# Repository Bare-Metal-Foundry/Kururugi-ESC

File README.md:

# ⚡ Kururugi - Electronic Speed Controller (ESC) ⚡ 

> 4/6S-ready • 64–96 kHz PWM • FOC/Six-Steps • Full bare-metal control

<p align="center">

  <br>

</p>

## ⚙️ Project overview

Kururugi is a high-performance ESC designed for FPV drones, built as a platform for low-level motor control, power electronics optimization, and embedded system experimentation.

It is developed within the **Bare Metal Foundry** initiative for autonomous racing drones, alongside the Shirley Flight Controller - forming a complete, fully controlled hardware and software stack.

This README provides an overview of the project and repository structure. Detailed hardware and ESC design information is available in: 📊 [Technical Specifications](docs/hw-kururugi-specs.md)

## ❓ Why Kururugi?

Most ESCs are closed, optimized for mass production - not understanding.

Kururugi is designed to:
- Push switching frequency limits (64 kHz in v1.0, targeting 96 kHz+ in future revisions)
- Provide full transparency and control over the motor stack (no black boxes)
- Enable high-speed bare-metal control
- Serve as a platform for developing and validating Six-Step and Field-Oriented Control (FOC)
- Bring together makers and engineers to explore, experiment, and push boundaries

👉 This is an research platform, not just an ESC.

## 🚢 Navigate the repo

> ⚠️ Documentation is still a work in progress. Detailed design notes and analysis will be added progressively.

### 📂 Not to miss documents:
- 🧩 **Hardware (KiCad)**: [KiCad project](hardware/Kururugi-ESC-KiCad/)
- 📊 **Design & Sizing**: [Design notes](docs\Kururugi-ESC-sizing.xlsx)
- 📊 **Technicals specifications**: [Documentation](docs/hw-kururugi-specs.md)
- 📤 **Exports**: [Schematics, PCB renders, STEP files](docs/exports)
- 📚 **Resources**: [Datasheets & Engineering Notes](resources/datasheets)

## 💻 Run it yourself

### 📟 H/W - PCB desgin
To get started, simply clone the repository and proceed to open the project on Kicad 9.0.4. All libraries are self containts so it is no more difficult than this.
```bash
git clone https://github.com/StepaneBinon/Kururugi-ESC-Dev-Board.git
```

### 📟 H/W — PCB Manufacturing

PCB fabrication and assembly are handled through JLCPCB. The minimum order quantity is 5 boards for PCB fabrication and 2 boards for assembly. With the selected options, the total cost is 255.13 € (295.01 USD).

Production files are available in [Production files](hardware/Kururugi-ESC-KiCad/Production/).  
When placing the order, use the parameters shown in [JLCPCB Options](hardware/Kururugi-ESC-KiCad/Production/JLCPCB%20-%20Options%20to%20use.png).

> ⚠️ Ensure BOM/CPL match and components are available before ordering.
> ⚠️ This design is provided as-is; no guarantee is made regarding functionality or performance.

### 🔢 S/W - Kururugi-6Step [WORK IN PROGRESS]

### 🔢 S/W - Kururugi-FOC [WORK IN PROGRESS]

## 🚀 Roadmap

### ⚡ Hardware
1. 🧪 **V1.0 Production & Bring-up** *(Apr 2026)*: First batch with JLCPCB, full electrical validation
2. 📖 **Design Documentation** *(May 2026)*: Complete breakdown of sizing, losses, and trade-offs
3. 🔌 **Multi-ESC Test Bench** *(Jun–Jul 2026)*: Dedicated rig for synchronized testing and stress scenarios
4. 🏁 **Drone Validation (V1)** *(Jul–Aug 2026)*: High-load FPV testing on 6-inch platform
5. 🤖 **Robotics Validation (V1)** *(Jul–Aug 2026)*: Differential drive platform for control robustness
6. 📝 **Technical Paper (V1 Results)** *(Sep 2026)*: Performance, efficiency, and design insights
7. ⚡ **V2 Hardware** *(2027)*: Sensor simplification, FOC/6-step optimization, possible 4-in-1

### 🧠 Software
1. 🏗 **Bare-Metal C++ Architecture** *(Apr–May 2026)*: Deterministic design, coding standards, HAL strategy (rewrite vs minimal use)
2. ⚙️ **6-Step Control (Baseline)** *(May–Jun 2026)*: Reliable startup and fallback mode
3. 🎯 **FOC Implementation** *(Jun–Aug 2026)*: High-efficiency, high-performance control
4. 📝 **Technical Paper (Control & Results)** *(Sep 2026)*: Control strategy, tuning, and comparison

## 🤝 How to Contribute

> Alone we go faster, together we go further.

Contributions are more than welcome, at all levels:

- 🐛 **Report issues**: bugs, design flaws, or unclear documentation
- 💡 **Suggest improvements**: hardware, firmware, or architecture ideas
- 🧪 **Test & validate**: share results, measurements, or flight data
- 📖 **Improve documentation**: clarify concepts, add explanations

### 📬 Get involved

- Open an issue for discussion  
- Submit a pull request  
- Share your insights or experiments 
- Join the **Bare Metal Foundry** discord here: https://discord.gg/e7CF2AZCN 

👉 If you're working on ESCs, power electronics, or embedded control, your feedback is highly valuable.

## 🪪 Licensing

### Hardware
Hardware design (schematics, PCB, KiCad) is licensed under CERN-OHL-S v2. This project is released as open hardware.
Any modifications or derived designs must be shared under the same license.

For commercial use, collaboration, or licensing inquiries, please reach out.

## 👤 Author

This project was originally created and is actively maintained by [Stepane Binon](https://github.com/StepaneBinon).

Parts of the documentation are generated with the assistance of AI tools to streamline development.

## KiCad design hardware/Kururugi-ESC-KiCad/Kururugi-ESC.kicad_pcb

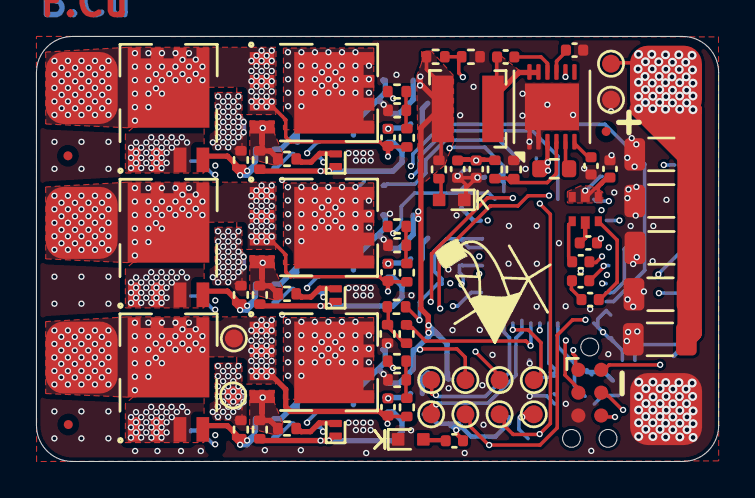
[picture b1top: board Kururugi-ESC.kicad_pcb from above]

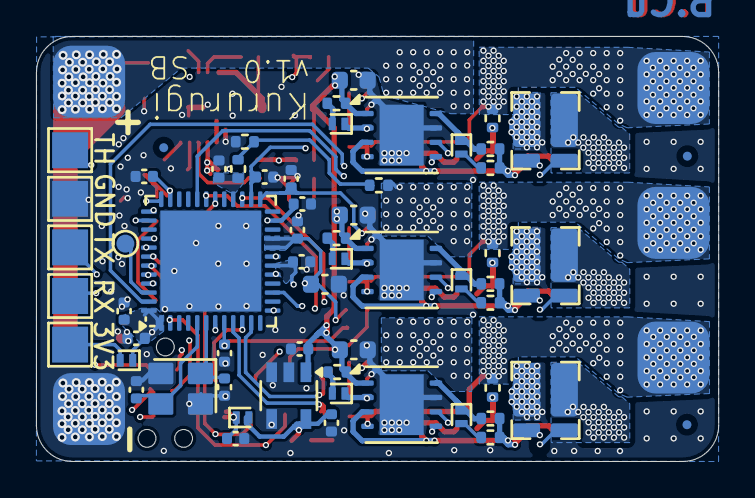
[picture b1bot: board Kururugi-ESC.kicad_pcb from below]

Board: 6 copper layers, 37.9 x 23.6 mm, 141 parts (60 on the bottom side), 85 nets.

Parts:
C1, C2, C3, C4, C5: 2.2u; C_1206_3216Metric
C6, C7, C8, C9, C15, C23, C24, C27, C30, C33: 100n; C_0402_1005Metric
C10, C11, C13, C14, C18, C21, C22: 1u; C_0402_1005Metric
C12, C16: 10n; C_0402_1005Metric
C17, C26, C29, C32: 1u; C_0603_1608Metric
C19, C20: 10p; C_0402_1005Metric
C25, C28, C31: 220n; C_0402_1005Metric
D1, D4: KT-0603W; LED_0603_1608Metric
D2, D3, D5, D6, D7, D8, D9, D10, D11, D12, D13: RB161QS-40T18R; Rohm_SMD1006
FID1, FID2, FID3, FID4, FID5, FID6: Fiducial_0.5mm_Mask1mm
J1, J2, J9, J10, J11: Conn_01x01; Phase4x4
J3, J4, J5, J6, J7: Conn_01x01; TestPoint_Pad_2.0x2.0mm
J8: JTAG_TC2030; Tag-Connect_TC2030-IDC-NL_2x03_P1.27mm_Vertical
L1: 22u; LVS404018-220M-N
LED1: 19-337C/RSBHGHC-A88/4T; SMD-B_19-337C_EVE
Q1, Q2, Q3, Q4, Q5, Q6: CSD18540Q5B
R1, R8: 22k; R_0402_1005Metric
R2, R12, R26, R37, R48: 33; R_0402_1005Metric
R3, R6, R27, R38, R49: 1k; R_0402_1005Metric
R4: 120k; R_0603_1608Metric
R5: 200k; R_0402_1005Metric
R7: 51k; R_0402_1005Metric
R9: 12k; R_0402_1005Metric
R10, R13, R14, R15, R16: 100; C_0402_1005Metric
R11, R20, R23, R24, R31, R34, R35, R42, R45, R46: 10k; R_0402_1005Metric
R17, R19, R21, R28, R30, R32, R39, R41, R43: 3.3; R_0402_1005Metric
R18, R22, R29, R33, R40, R44: 10; R_0402_1005Metric
R25, R36, R47: 0.5m; HoBB1216-5W-0.5mR-1
TH1: Thermistor_NTC; R_0402_1005Metric
TP1, TP2, TP3, TP4, TP5, TP6, TP7, TP8, TP9, TP10, TP11, TP12, TP13: TestPoint; TestPoint_Pad_D1.0mm
U1: STM32G474CEU6
U2: LM5160A; LM5160ADNTR
U3: TPS7B92033; TI-SOT-23 (5p)
U4, U5, U6: 2EDL8024
X1: 16MHz; YXC-X322516MLB4SI

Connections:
3V3: C7.1, C8.1, C9.1, C15.1, C16.1, C17.1, C18.2, C24.1, D2.1 (K), D3.1 (K), J8.1 (VCC), LED1.2, LED1.4, LED1.6, R11.1, TP13.1, U1.1 (VBAT), U1.20 (VREF+), U1.21 (VDDA), U1.23 (VDD), U1.35 (VDD), U1.48 (VDD)
3V3_UART: D2.2 (A), J5.1
/3V3_LDO: C21.1, D3.2 (A), R10.1, U3.5 (OUT)
/BOOT0: TP1.1, U1.46 (PB8-BOOT0)
/FB: R7.2, R9.1, U2.8 (FB)
/HSE_IN: C19.1, U1.5 (PF0-OSC_IN), X1.3
/HSE_OUT: C20.1, U1.6 (PF1-OSC_OUT), X1.1
/ISENS1+: R25.1, U1.17 (PB0)
/ISENS1-: R25.4, U1.19 (PB2)
/ISENS2+: R36.1, U1.15 (PA7)
/ISENS2-: R36.4, U1.13 (PA5)
/ISENS3+: R47.1, TP7.1, U1.9 (PA1)
/ISENS3-: R47.4, TP9.1, U1.11 (PA3)
/JTAG_NRST: J8.3 (~RESET), U1.7 (PG10-NRST)
/OPAMP_VOUT_ISENS3: TP8.1, U1.10 (PA2)
/PHASE 1/GH: Q1.2 (G), R18.2, R19.2, R20.1
/PHASE 1/GL: Q2.2 (G), R21.2, R22.2, R23.1
/PHASE 1/HB: C25.1, D5.1 (K), U4.2 (HB)
/PHASE 1/HO: D6.1 (K), R19.1, U4.3 (HO)
/PHASE 1/LO: D7.1 (K), R21.1, U4.8 (LO)
/PHASE 1/LS: Q2.3 (S), R25.2
/PHASE 1/VS: R24.2, R26.2, R27.2
/PHASE 2/GH: Q3.2 (G), R29.2, R30.2, R31.1
/PHASE 2/GL: Q4.2 (G), R32.2, R33.2, R34.1
/PHASE 2/HB: C28.1, D8.1 (K), U5.2 (HB)
/PHASE 2/HO: D9.1 (K), R30.1, U5.3 (HO)
/PHASE 2/LO: D10.1 (K), R32.1, U5.8 (LO)
/PHASE 2/LS: Q4.3 (S), R36.2
/PHASE 2/VS: R35.2, R37.2, R38.2
/PHASE 3/GH: Q5.2 (G), R40.2, R41.2, R42.1
/PHASE 3/GL: Q6.2 (G), R43.2, R44.2, R45.1
/PHASE 3/HB: C31.1, D11.1 (K), U6.2 (HB)
/PHASE 3/HO: D12.1 (K), R41.1, U6.3 (HO)
/PHASE 3/LO: D13.1 (K), R43.1, U6.8 (LO)
/PHASE 3/LS: Q6.3 (S), R47.2
/PHASE 3/VS: R46.2, R48.2, R49.2
/PWM1: U1.32 (PA10), U4.5 (HI)
/PWM1N: U1.47 (PB9), U4.6 (LI)
/PWM2: U1.31 (PA9), U5.5 (HI)
/PWM2N: U1.27 (PB14), U5.6 (LI)
/PWM3: TP6.1, U1.30 (PA8), U6.5 (HI)
/PWM3N: TP5.1, U1.2 (PC13), U6.6 (LI)
/RGB_B: R16.1, U1.42 (PB4)
/RGB_G: R15.1, U1.40 (PC11)
/RGB_R: R13.1, U1.43 (PB5)
/RON: R4.2, U2.5 (RON)
/SS: C14.1, U2.6 (SS)
/SW: C12.1, L1.1, U2.11 (SW), U2.12 (SW)
/SWCLK: J8.4 (SWCLK), U1.37 (PA14)
/SWDIO: J8.2 (SWDIO), U1.36 (PA13)
/SWO: J8.6 (SWO), U1.41 (PB3)
/THROTTLE_CMD: J6.1, U1.38 (PA15)
/TSENS: C23.1, R12.1, U1.8 (PA0)
/UART_RX: J3.1, U1.45 (PB7)
/UART_TX: J4.1, U1.44 (PB6)
/UVLO: R5.2, R8.1, U2.4 (EN/UVLO)
/VCC: C13.1, U2.9 (VCC)
/VSENS1: C27.1, R26.1, U1.26 (PB13)
/VSENS2: C30.1, R37.1, U1.25 (PB12)
/VSENS3: C33.1, R48.1, TP11.1, U1.18 (PB1)
/VSENSBAT: C6.1, R2.1, U1.28 (PB15)
GND: C1.2, C2.2, C3.2, C4.2, C5.2, C6.2, C7.2, C8.2, C9.2, C10.2, C11.2, C13.2, C14.2, C15.2, C16.2, C17.2, C18.1, C19.2, C20.2, C21.2, C22.2, C23.2, C24.2, C26.2, C27.2, C29.2, C30.2, C32.2, C33.2, D1.1 (K), D4.1 (K), J2.1, J7.1, J8.5 (GND), R3.2, R8.2, R9.2, R23.2, R25.3, R27.1, R34.2, R36.3, R38.1, R45.2, R47.3, R49.1, TH1.2, TP3.1, TP4.1, U1.PAD (VSS), U2.1 (AGND), U2.2 (PGND), U2.PAD (AGND), U3.2 (GND), U3.3 (NC), U3.4 (NC), U4.7 (VSS), U4.PAD (VSS), U5.7 (VSS), U5.PAD (VSS), U6.7 (VSS), U6.PAD (VSS), X1.2, X1.4
unnamed: D1.2 (A), R6.2
unnamed: D4.2 (A), R10.2
unnamed: D5.2 (A), R17.2
unnamed: D6.2 (A), R18.1
unnamed: D7.2 (A), R22.1
unnamed: D8.2 (A), R28.2
unnamed: D9.2 (A), R29.1
unnamed: D10.2 (A), R33.1
unnamed: D11.2 (A), R39.2
unnamed: D12.2 (A), R40.1
unnamed: D13.2 (A), R44.1
unnamed: LED1.1, R14.1
unnamed: LED1.3, R15.2
unnamed: LED1.5, R16.2
unnamed: R1.2, R2.2, R3.1
unnamed: R11.2, R12.2, TH1.1
unnamed: R13.2, R14.2
unnamed: C12.2, U2.10 (BST)
PH1: C25.2, J9.1, Q1.3 (S), Q2.1 (D), R20.2, R24.1, U4.4 (HS)
PH2: C28.2, J10.1, Q3.3 (S), Q4.1 (D), R31.2, R35.1, U5.4 (HS)
PH3: C31.2, J11.1, Q5.3 (S), Q6.1 (D), R42.2, R46.1, TP12.1, U6.4 (HS)
VBAT: C1.1, C2.1, C3.1, C4.1, C5.1, C10.1, C11.1, J1.1, Q1.1 (D), Q3.1 (D), Q5.1 (D), R1.1, R4.1, R5.1, TP2.1, U2.3 (VIN)
VBUCK: C22.1, C26.1, C29.1, C32.1, L1.2, R6.1, R7.1, R17.1, R28.1, R39.1, TP10.1, U3.1 (VIN), U4.1 (VDD), U5.1 (VDD), U6.1 (VDD)

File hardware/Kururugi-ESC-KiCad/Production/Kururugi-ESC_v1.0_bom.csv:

Designator,Footprint,Quantity,Value,LCSC Part #
"C1, C2, C3, C4, C5",1206,5,2.2u,C50254
"C10, C11, C13, C14, C18, C21, C22",0402,7,1u,C52923
"C12, C16",0402,2,10n,C15195
"C15, C23, C24, C27, C30, C33, C6, C7, C8, C9",0402,10,100n,C1525
"C17, C26, C29, C32",0603,4,1u,C15849
"C19, C20",0402,2,10p,C32949
"C25, C28, C31",0402,3,220n,C16772
"D1, D4",0603,2,KT-0603W,C2290
"D10, D11, D12, D13, D2, D3, D5, D6, D7, D8, D9",Rohm_SMD1006,11,RB161QS-40T18R, C2837790
"J1, J10, J11, J2, J9",Phase4x4,5,Conn_01x01,
"J3, J4, J5, J6, J7",TestPoint_Pad_2.0x2.0mm,5,Conn_01x01,
L1,LVS404018-220M-N,1,22u, C116614
LED1,SMD-B_19-337C_EVE,1,19-337C/RSBHGHC-A88/4T,C3019536
"Q1, Q2, Q3, Q4, Q5, Q6",CSD18540Q5B,6,CSD18540Q5B,C86513
"R1, R8",0402,2,22k,C25768
"R10, R13, R14, R15, R16",0402,5,100,C25076
"R11, R20, R23, R24, R31, R34, R35, R42, R45, R46",0402,10,10k,C25744
"R12, R2, R26, R37, R48",0402,5,33,C25105
"R17, R19, R21, R28, R30, R32, R39, R41, R43",0402,9,3.3,C25165
"R18, R22, R29, R33, R40, R44",0402,6,10,C25077
"R25, R36, R47",HoBB1216-5W-0.5mR-1,3,0.5m,C17701556
"R27, R3, R38, R49, R6",0402,5,1k,C11702
R4,0603,1,120k,C25808
R5,0402,1,200k,C25764
R7,0402,1,51k,C25794
R9,0402,1,12k,C25752
TH1,0402,1,Thermistor_NTC,C209959
"TP1, TP10, TP11, TP12, TP13, TP2, TP3, TP4, TP5, TP6, TP7, TP8, TP9",TestPoint_Pad_D1.0mm,13,TestPoint,
U1,STM32G474CEU6,1,STM32G474CEU6, C1235412
U2,LM5160ADNTR,1,LM5160A,C473375
U3,TI-SOT-23 (5p),1,TPS7B92033,C32353919
"U4, U5, U6",2EDL8024,3,2EDL8024, C3655215
X1,YXC-X322516MLB4SI,1,16MHz,C13738

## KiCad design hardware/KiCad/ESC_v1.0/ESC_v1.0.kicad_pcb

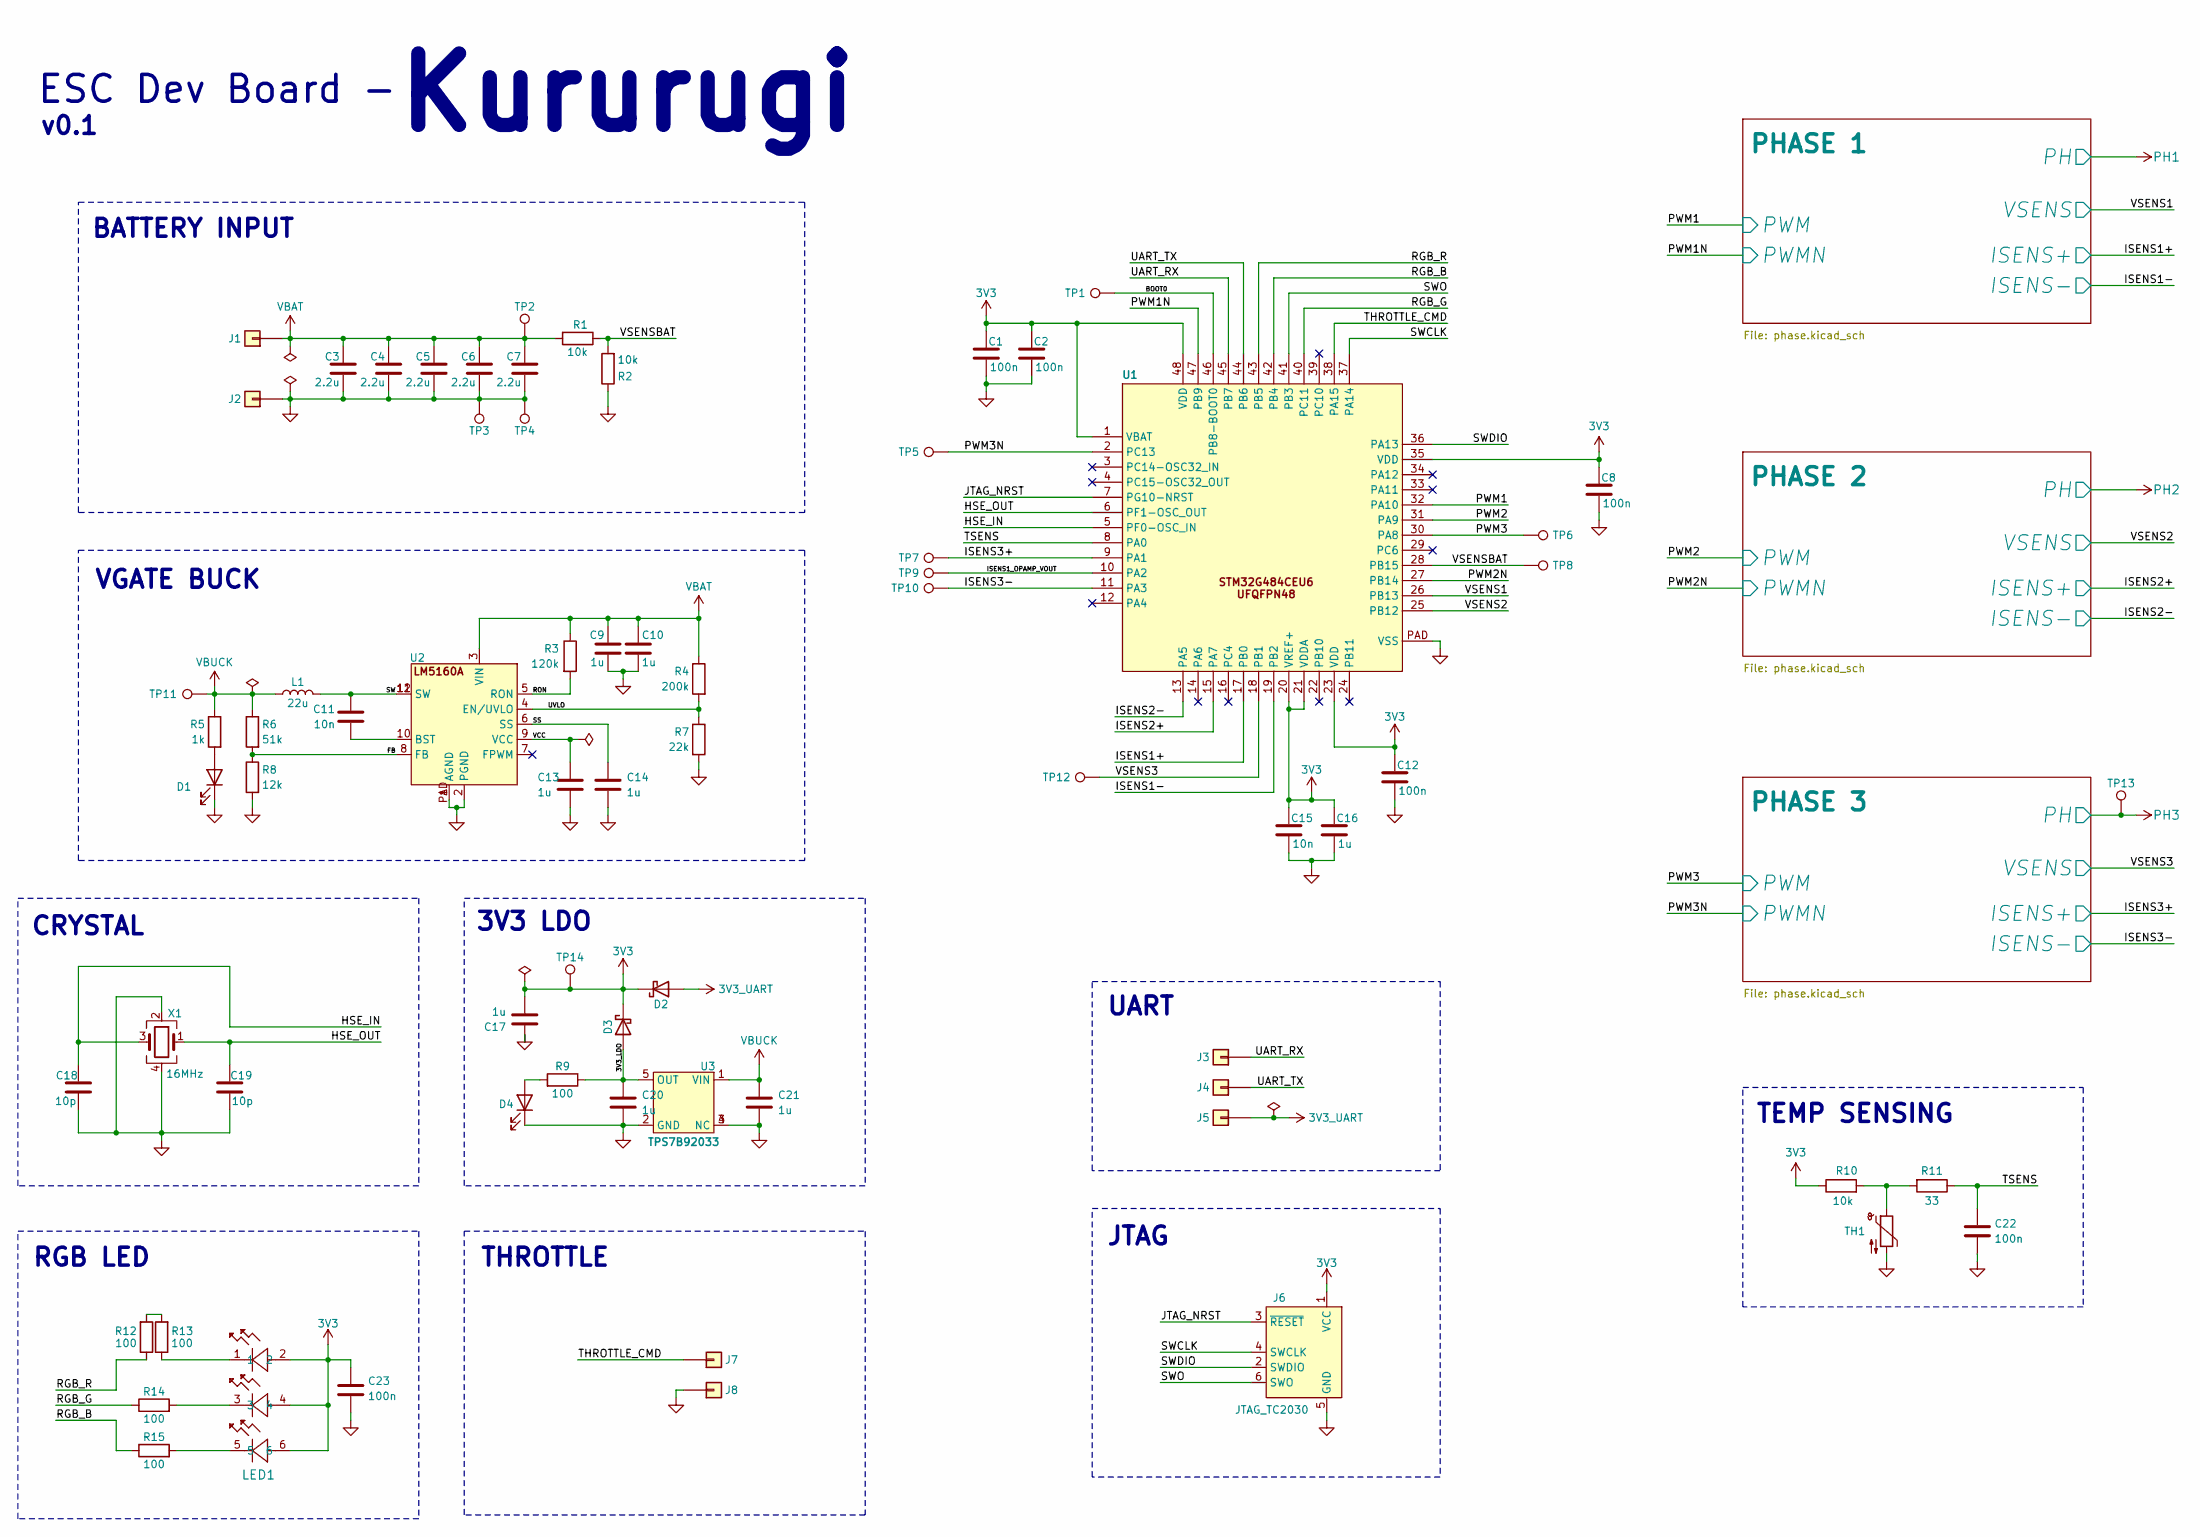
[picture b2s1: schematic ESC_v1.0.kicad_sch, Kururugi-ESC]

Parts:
C1, C2, C8, C12, C22, C23: 100n; C_0402_1005Metric; Manufacturer Part Number CL05B104KO5NNNC; LCSC C1525
C3, C4, C5, C6, C7: 2.2u; C_1206_3216Metric; Manufacturer Part Number CL31B225KBHNNNE; LCSC C50254
C9, C10, C13, C14, C17, C20, C21: 1u; C_0402_1005Metric; Manufacturer Part Number CL05A105KA5NQNC; LCSC C52923
C11, C15: 10n; C_0402_1005Metric; Manufacturer Part Number CL05B103KB5NNNC; LCSC C15195
C16: 1u; C_0603_1608Metric; Manufacturer Part Number CL10A105KB8NNNC; LCSC C15849
C18, C19: 10p; C_0402_1005Metric; Manufacturer Part Number CL05C100JB5NNNC; LCSC C32949
D1, D4: KT-0603W; LED_0603_1608Metric; Manufacturer Part Number KT-0603W; LCSC C2290
D2, D3: RB161QS-40T18R; Rohm_SMD1006; Manufacturer Part Number RB161QS-40T18R; LCSC C2837790
J1, J2: Conn_01x01; Phase4x4
J3, J4, J5, J7, J8: Conn_01x01; TestPoint_Pad_2.0x2.0mm
J6: JTAG_TC2030; Tag-Connect_TC2030-IDC-NL_2x03_P1.27mm_Vertical
L1: 22u; Chilisin_Elec_SMD,4x4mm; Manufacturer Part Number LVS404018-220M-N; LCSC C116614
LED1: 19-337C/RSBHGHC-A88/4T; SMD-B_19-337C_EVE; Manufacturer Part Number 19-337C/RSBHGHC-A88/4T; LCSC C3019536
R1, R2, R10: 10k; R_0402_1005Metric; Manufacturer Part Number 0402WGF1002TCE; LCSC C25744
R3: 120k; R_0603_1608Metric; Manufacturer Part Number 0603WAF1203T5E; LCSC C25808
R4: 200k; R_0402_1005Metric; Manufacturer Part Number 0402WGF2003TCE; LCSC C25764
R5: 1k; R_0402_1005Metric; Manufacturer Part Number 0402WGF1001TCE; LCSC C11702
R6: 51k; R_0402_1005Metric; Manufacturer Part Number 0402WGF5102TCE; LCSC C25794
R7: 22k; R_0402_1005Metric; Manufacturer Part Number 0402WGF2202TCE; LCSC C25768
R8: 12k; R_0402_1005Metric; Manufacturer Part Number 0402WGF1202TCE; LCSC C25752
R9, R12, R13, R14, R15: 100; R_0402_1005Metric; Manufacturer Part Number 0402WGF1000TCE; LCSC C25076
R11: 33; R_0402_1005Metric; Manufacturer Part Number 0402WGF330JTCE; LCSC C25752
TH1: Thermistor_NTC; R_0402_1005Metric; Manufacturer Part Number NTCG103JF103FT1; LCSC C209959
TP1, TP2, TP3, TP4, TP5, TP6, TP7, TP8, TP9, TP10, TP11, TP12, TP13, TP14: TestPoint; TestPoint_Pad_D1.0mm
U1: STM32G484CEU6; QFN-48-1EP_7x7mm_P0.5mm_EP5.6x5.6mm; Manufacturer Part Number STM32G484CEU6; LCSC C1342230
U2: LM5160A; WSON-12-1EP_4x4mm_P0.5mm_EP2.6x3mm; Manufacturer Part Number LM5160ADNTR; LCSC C473375
U3: TPS7B92033; TI-SOT-23 (5p); Manufacturer Part Number TPS7B92033DBVR; LCSC C32353919
X1: 16MHz; YXC-X322516MLB4SI; Manufacturer Part Number X322516MLB4SI; LCSC C13738

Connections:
3V3: C1.1, C2.1, C8.1, C12.1, C15.1, C16.1, C17.2, C23.1, D2.1 (K), D3.1 (K), J6.1 (VCC), LED1.2, LED1.4, LED1.6, R10.1, TP14.1, U1.1 (VBAT), U1.20 (VREF+), U1.21 (VDDA), U1.23 (VDD), U1.35 (VDD), U1.48 (VDD)
3V3_UART: D2.2 (A), J5.1
/3V3_LDO: C20.1, D3.2 (A), R9.1, U3.5 (OUT)
/BOOT0: TP1.1, U1.46 (PB8-BOOT0)
/FB: R6.2, R8.1, U2.8 (FB)
/HSE_IN: C18.1, U1.5 (PF0-OSC_IN), X1.3
/HSE_OUT: C19.1, U1.6 (PF1-OSC_OUT), X1.1
/ISENS1+: U1.17 (PB0); also elsewhere on the board
/ISENS1-: U1.19 (PB2); also elsewhere on the board
/ISENS1_OPAMP_VOUT: TP9.1, U1.10 (PA2)
/ISENS2+: U1.15 (PA7); also elsewhere on the board
/ISENS2-: U1.13 (PA5); also elsewhere on the board
/ISENS3+: TP7.1, U1.9 (PA1); also elsewhere on the board
/ISENS3-: TP10.1, U1.11 (PA3); also elsewhere on the board
/JTAG_NRST: J6.3 (~RESET), U1.7 (PG10-NRST)
/PWM1: U1.32 (PA10); also elsewhere on the board
/PWM1N: U1.47 (PB9); also elsewhere on the board
/PWM2: U1.31 (PA9); also elsewhere on the board
/PWM2N: U1.27 (PB14); also elsewhere on the board
/PWM3: TP6.1, U1.30 (PA8); also elsewhere on the board
/PWM3N: TP5.1, U1.2 (PC13); also elsewhere on the board
/RGB_B: R15.1, U1.42 (PB4)
/RGB_G: R14.1, U1.40 (PC11)
/RGB_R: R12.1, U1.43 (PB5)
/RON: R3.2, U2.5 (RON)
/SS: C14.1, U2.6 (SS)
/SW: C11.1, L1.1, U2.11 (SW), U2.12 (SW)
/SWCLK: J6.4 (SWCLK), U1.37 (PA14)
/SWDIO: J6.2 (SWDIO), U1.36 (PA13)
/SWO: J6.6 (SWO), U1.41 (PB3)
/THROTTLE_CMD: J7.1, U1.38 (PA15)
/TSENS: C22.1, R11.1, U1.8 (PA0)
/UART_RX: J3.1, U1.45 (PB7)
/UART_TX: J4.1, U1.44 (PB6)
/UVLO: R4.2, R7.1, U2.4 (EN/UVLO)
/VCC: C13.1, U2.9 (VCC)
/VSENS1: U1.26 (PB13); also elsewhere on the board
/VSENS2: U1.25 (PB12); also elsewhere on the board
/VSENS3: TP12.1, U1.18 (PB1); also elsewhere on the board
/VSENSBAT: R1.1, R2.2, TP8.1, U1.28 (PB15)
GND: C1.2, C2.2, C3.2, C4.2, C5.2, C6.2, C7.2, C8.2, C9.2, C10.2, C12.2, C13.2, C14.2, C15.2, C16.2, C17.1, C18.2, C19.2, C20.2, C21.2, C22.2, C23.2, D1.1 (K), D4.1 (K), J2.1, J6.5 (GND), J8.1, R2.1, R7.2, R8.2, TH1.2, TP3.1, TP4.1, U1.PAD (VSS), U2.1 (AGND), U2.2 (PGND), U2.PAD (AGND), U3.2 (GND), U3.3 (NC), U3.4 (NC), X1.2, X1.4; also elsewhere on the board
unnamed: D1.2 (A), R5.2
unnamed: D4.2 (A), R9.2
unnamed: LED1.1, R13.1
unnamed: LED1.3, R14.2
unnamed: LED1.5, R15.2
unnamed: R10.2, R11.2, TH1.1
unnamed: R12.2, R13.2
unnamed: C11.2, U2.10 (BST)
PH3: TP13.1; also elsewhere on the board
VBAT: C3.1, C4.1, C5.1, C6.1, C7.1, C9.1, C10.1, J1.1, R1.2, R3.1, R4.1, TP2.1, U2.3 (VIN); also elsewhere on the board
VBUCK: C21.1, L1.2, R5.1, R6.1, TP11.1, U3.1 (VIN); also elsewhere on the board

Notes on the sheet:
Kururugi
UART
JTAG
THROTTLE
RGB LED
CRYSTAL
BATTERY INPUT
VGATE BUCK
TEMP SENSING
ESC Dev Board -
3V3 LDO
${REVISION}

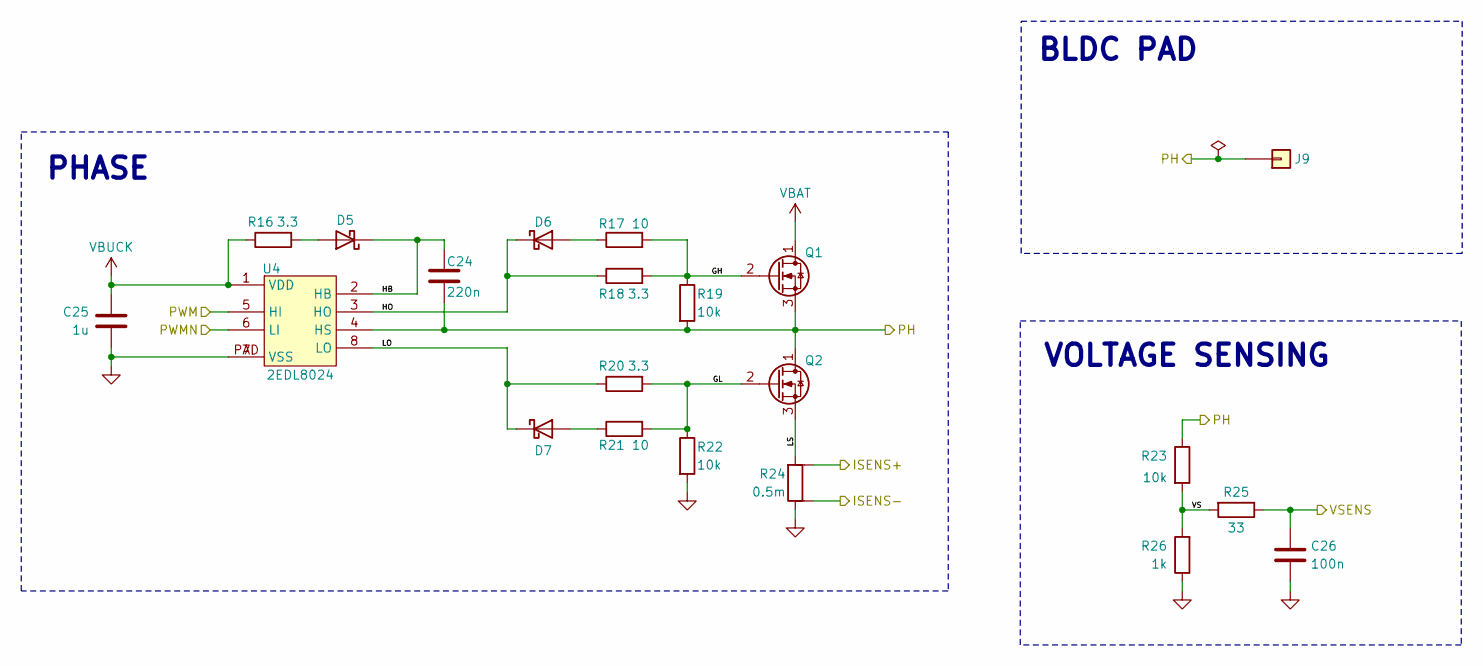
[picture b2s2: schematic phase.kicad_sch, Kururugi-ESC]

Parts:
C24: 220n; C_0402_1005Metric; Manufacturer Part Number CL05B224KO5NNNC; LCSC C16772
C25: 1u; C_0603_1608Metric; Manufacturer Part Number CL10A105KB8NNNC; LCSC C15849
C26: 100n; C_0402_1005Metric; Manufacturer Part Number CL05B104KO5NNNC; LCSC C1525
D5, D6, D7: RB161QS-40T18R; Rohm_SMD1006; Manufacturer Part Number RB161QS-40T18R; LCSC C2837790
J9: Conn_01x01; Phase4x4
Q1, Q2: CSD18540Q5B; TRANS_CSD18540Q5B; Manufacturer Part Number CSD18540Q5B; LCSC C86513
R16, R18, R20: 3.3; R_0402_1005Metric; Manufacturer Part Number 0402WGJ033JTCE; LCSC C25165
R17, R21: 10; R_0402_1005Metric; Manufacturer Part Number 0402WGF100JTCE; LCSC C25077
R19, R22, R23: 10k; R_0402_1005Metric; Manufacturer Part Number 0402WGF1002TCE; LCSC C25744
R24: 0.5m; Kelvin Shunt 1216 (3038); Manufacturer Part Number HoBB1216-5W-0.5mR-1%; LCSC C17701556
R25: 33; R_0402_1005Metric; Manufacturer Part Number 0402WGF330JTCE; LCSC C25752
R26: 1k; R_0402_1005Metric; Manufacturer Part Number 0402WGF1001TCE; LCSC C11702
U4: 2EDL8024; 2EDL8x2x_PG-VDSON-8-4; Manufacturer Part Number 2EDL8024G; LCSC C3655215

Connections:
/ISENS1+: R24.1; also elsewhere on the board
/ISENS1-: R24.4; also elsewhere on the board
/PHASE 1/GH: Q1.2 (G), R17.2, R18.2, R19.1
/PHASE 1/GL: Q2.2 (G), R20.2, R21.2, R22.1
/PHASE 1/HB: C24.1, D5.1 (K), U4.2 (HB)
/PHASE 1/HO: D6.1 (K), R18.1, U4.3 (HO)
/PHASE 1/LO: D7.1 (K), R20.1, U4.8 (LO)
/PHASE 1/LS: Q2.3 (S), R24.2
/PHASE 1/VS: R23.2, R25.2, R26.2
/PWM1: U4.5 (HI); also elsewhere on the board
/PWM1N: U4.6 (LI); also elsewhere on the board
/VSENS1: C26.1, R25.1; also elsewhere on the board
GND: C25.2, C26.2, R22.2, R24.3, R26.1, U4.7 (VSS), U4.PAD (VSS); also elsewhere on the board
unnamed: D5.2 (A), R16.2
unnamed: D6.2 (A), R17.1
unnamed: D7.2 (A), R21.1
PH1: C24.2, J9.1, Q1.3 (S), Q2.1 (D), R19.2, R23.1, U4.4 (HS)
VBAT: Q1.1 (D); also elsewhere on the board
VBUCK: C25.1, R16.1, U4.1 (VDD); also elsewhere on the board

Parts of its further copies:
C27, C30: 220n; C_0402_1005Metric; Manufacturer Part Number CL05B224KO5NNNC; LCSC C16772
C28, C31: 1u; C_0603_1608Metric; Manufacturer Part Number CL10A105KB8NNNC; LCSC C15849
C29, C32: 100n; C_0402_1005Metric; Manufacturer Part Number CL05B104KO5NNNC; LCSC C1525
D8, D9, D10, D11, D12, D13: RB161QS-40T18R; Rohm_SMD1006; Manufacturer Part Number RB161QS-40T18R; LCSC C2837790
J10, J11: Conn_01x01; Phase4x4
Q3, Q4, Q5, Q6: CSD18540Q5B; TRANS_CSD18540Q5B; Manufacturer Part Number CSD18540Q5B; LCSC C86513
R27, R29, R31, R38, R40, R42: 3.3; R_0402_1005Metric; Manufacturer Part Number 0402WGJ033JTCE; LCSC C25165
R28, R32, R39, R43: 10; R_0402_1005Metric; Manufacturer Part Number 0402WGF100JTCE; LCSC C25077
R30, R33, R34, R41, R44, R45: 10k; R_0402_1005Metric; Manufacturer Part Number 0402WGF1002TCE; LCSC C25744
R35, R46: 0.5m; Kelvin Shunt 1216 (3038); Manufacturer Part Number HoBB1216-5W-0.5mR-1%; LCSC C17701556
R36, R47: 33; R_0402_1005Metric; Manufacturer Part Number 0402WGF330JTCE; LCSC C25752
R37, R48: 1k; R_0402_1005Metric; Manufacturer Part Number 0402WGF1001TCE; LCSC C11702
U5, U6: 2EDL8024; 2EDL8x2x_PG-VDSON-8-4; Manufacturer Part Number 2EDL8024G; LCSC C3655215

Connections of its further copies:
/ISENS2+: R35.1; also elsewhere on the board
/ISENS2-: R35.4; also elsewhere on the board
/ISENS3+: R46.1; also elsewhere on the board
/ISENS3-: R46.4; also elsewhere on the board
/PHASE 2/GH: Q3.2 (G), R28.2, R29.2, R30.1
/PHASE 2/GL: Q4.2 (G), R31.2, R32.2, R33.1
/PHASE 2/HB: C27.1, D8.1 (K), U5.2 (HB)
/PHASE 2/HO: D9.1 (K), R29.1, U5.3 (HO)
/PHASE 2/LO: D10.1 (K), R31.1, U5.8 (LO)
/PHASE 2/LS: Q4.3 (S), R35.2
/PHASE 2/VS: R34.2, R36.2, R37.2
/PHASE 3/GH: Q5.2 (G), R39.2, R40.2, R41.1
/PHASE 3/GL: Q6.2 (G), R42.2, R43.2, R44.1
/PHASE 3/HB: C30.1, D11.1 (K), U6.2 (HB)
/PHASE 3/HO: D12.1 (K), R40.1, U6.3 (HO)
/PHASE 3/LO: D13.1 (K), R42.1, U6.8 (LO)
/PHASE 3/LS: Q6.3 (S), R46.2
/PHASE 3/VS: R45.2, R47.2, R48.2
/PWM2: U5.5 (HI); also elsewhere on the board
/PWM2N: U5.6 (LI); also elsewhere on the board
/PWM3: U6.5 (HI); also elsewhere on the board
/PWM3N: U6.6 (LI); also elsewhere on the board
/VSENS2: C29.1, R36.1; also elsewhere on the board
/VSENS3: C32.1, R47.1; also elsewhere on the board
GND: C28.2, C29.2, C31.2, C32.2, R33.2, R35.3, R37.1, R44.2, R46.3, R48.1, U5.7 (VSS), U5.PAD (VSS), U6.7 (VSS), U6.PAD (VSS); also elsewhere on the board
unnamed: D8.2 (A), R27.2
unnamed: D9.2 (A), R28.1
unnamed: D10.2 (A), R32.1
unnamed: D11.2 (A), R38.2
unnamed: D12.2 (A), R39.1
unnamed: D13.2 (A), R43.1
PH2: C27.2, J10.1, Q3.3 (S), Q4.1 (D), R30.2, R34.1, U5.4 (HS)
PH3: C30.2, J11.1, Q5.3 (S), Q6.1 (D), R41.2, R45.1, U6.4 (HS); also elsewhere on the board
VBAT: Q3.1 (D), Q5.1 (D); also elsewhere on the board
VBUCK: C28.1, C31.1, R27.1, R38.1, U5.1 (VDD), U6.1 (VDD); also elsewhere on the board

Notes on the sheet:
PHASE
BLDC PAD
VOLTAGE SENSING

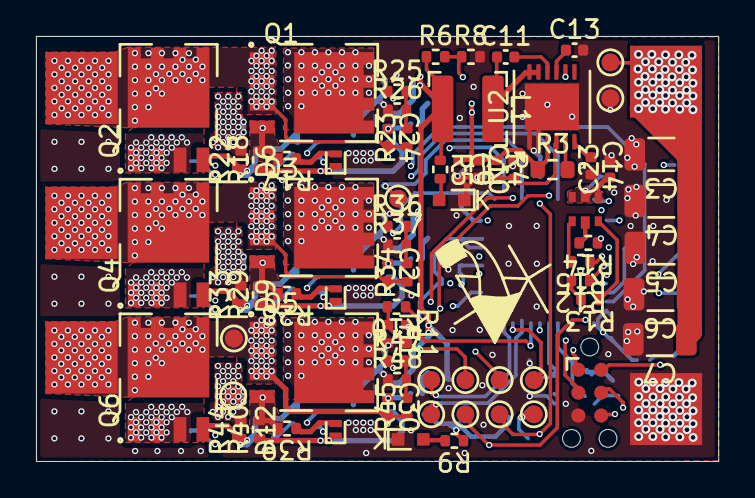
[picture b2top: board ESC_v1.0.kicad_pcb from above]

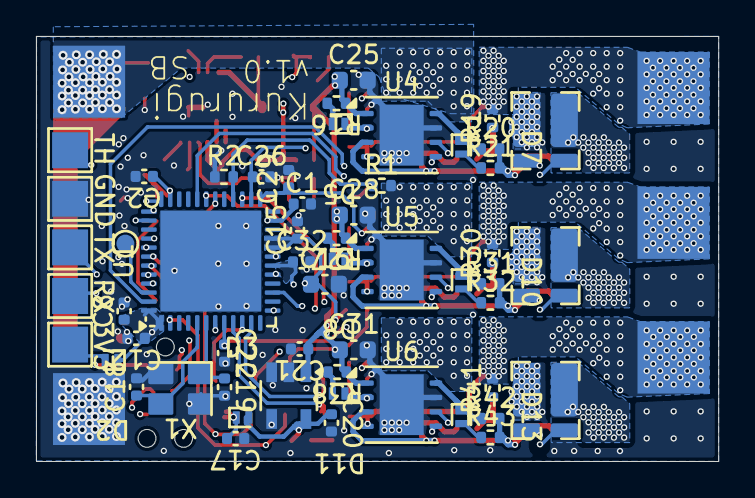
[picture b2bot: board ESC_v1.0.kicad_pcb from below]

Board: 6 copper layers, 37.9 x 23.6 mm, 134 parts (55 on the bottom side), 84 nets.

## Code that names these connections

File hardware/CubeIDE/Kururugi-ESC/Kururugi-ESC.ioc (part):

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Mcu.Name=STM32G484CEUx
Mcu.Package=UFQFPN48
Mcu.UserName=STM32G484CEUx
PA0.GPIOParameters=GPIO_Label
PA0.GPIO_Label=TSENS
PA0.Mode=IN1-Single-Ended
PA0.Signal=ADC2_IN1
PA1.GPIOParameters=GPIO_Label
PA1.GPIO_Label=AMP1VINP_ISENS3+
PA1.Mode=PGA Connected-INVERTINGINPUT_IO0_BIAS
PA1.Signal=OPAMP1_VINP
PA10.GPIOParameters=GPIO_Label
PA10.GPIO_Label=TIM1CH3_PH1
PA10.Signal=S_TIM1_CH3
PA13.GPIOParameters=GPIO_Label
PA13.GPIO_Label=SWDIO
PA13.Mode=Trace_Asynchronous_SW
PA13.Signal=SYS_JTMS-SWDIO
PA14.GPIOParameters=GPIO_Label
PA14.GPIO_Label=SWCLK
PA14.Mode=Trace_Asynchronous_SW
PA14.Signal=SYS_JTCK-SWCLK
PA15.GPIOParameters=GPIO_Label
PA15.GPIO_Label=TIM2CH1_TH
PA15.Signal=S_TIM2_CH1
PA2.GPIOParameters=GPIO_Label
PA2.GPIO_Label=AMP1VOUT_ISENS3
PA2.Mode=PGA Connected-INVERTINGINPUT_IO0_BIAS
PA2.Signal=OPAMP1_VOUT
PA3.GPIOParameters=GPIO_Label
PA3.GPIO_Label=AMP1VINM_ISENS3-
PA3.Mode=PGA Connected-INVERTINGINPUT_IO0_BIAS
PA3.Signal=OPAMP1_VINM0
PA5.GPIOParameters=GPIO_Label
PA5.GPIO_Label=AMP2VINM_ISENS2-
PA5.Mode=PGA Internally connected_IO
PA5.Signal=OPAMP2_VINM0
PA7.GPIOParameters=GPIO_Label
PA7.GPIO_Label=AMP2VINP_ISENS2+
PA7.Mode=PGA Internally connected_IO
PA7.Signal=OPAMP2_VINP
PA8.GPIOParameters=GPIO_Label
PA8.GPIO_Label=TIM1CH1_PH3
PA8.Signal=S_TIM1_CH1
PA9.GPIOParameters=GPIO_Label
PA9.GPIO_Label=TIM1CH2_PH2
PA9.Signal=S_TIM1_CH2
PB0.GPIOParameters=GPIO_Label
PB0.GPIO_Label=AMP3VINP_ISENS1+
PB0.Mode=PGA Internally connected_IO
PB0.Signal=OPAMP3_VINP
PB1.GPIOParameters=GPIO_Label
PB1.GPIO_Label=ADC1IN12_VSENS3
PB1.Mode=IN12-Single-Ended
PB1.Signal=ADC1_IN12
PB12.GPIOParameters=GPIO_Label
PB12.GPIO_Label=ADC4IN3_VSENS2
PB12.Mode=IN3-Single-Ended
PB12.Signal=ADC4_IN3
PB13.GPIOParameters=GPIO_Label
PB13.GPIO_Label=ADC3IN5_VSENS1
PB13.Mode=IN5-Single-Ended
PB13.Signal=ADC3_IN5
PB14.GPIOParameters=GPIO_Label
PB14.GPIO_Label=TIM1CH2N_PH2N
PB14.Mode=PWM Generation2 CH2 CH2N
PB14.Signal=TIM1_CH2N
PB15.GPIOParameters=GPIO_Label
PB15.GPIO_Label=ADC4IN5_VBATSENS
PB15.Mode=IN5-Single-Ended
PB15.Signal=ADC4_IN5
PB2.GPIOParameters=GPIO_Label
PB2.GPIO_Label=AMP3VINM_ISENS1-
PB2.Mode=PGA Internally connected_IO
PB2.Signal=OPAMP3_VINM0
PB3.GPIOParameters=GPIO_Label
PB3.GPIO_Label=SWO
PB3.Mode=Trace_Asynchronous_SW
PB3.Signal=SYS_JTDO-SWO
PB4.GPIOParameters=GPIO_Label
PB4.GPIO_Label=RGB_B
PB4.Signal=GPIO_Output
PB5.GPIOParameters=GPIO_Label
PB5.GPIO_Label=RGB_R
PB5.Signal=GPIO_Output
PB6.GPIOParameters=GPIO_Label
PB6.GPIO_Label=UART_TX
PB6.Mode=Asynchronous
PB6.Signal=USART1_TX
PB7.GPIOParameters=GPIO_Label
PB7.GPIO_Label=UART_RX
PB7.Mode=Asynchronous
PB7.Signal=USART1_RX
PB9.GPIOParameters=GPIO_Label
PB9.GPIO_Label=TIM1CH3N_PH1N
PB9.Mode=Output Compare3 CH3 CH3N
PB9.Signal=TIM1_CH3N
PC11.GPIOParameters=GPIO_Label
PC11.GPIO_Label=RGB_G
PC11.Signal=GPIO_Output
PC13.GPIOParameters=GPIO_Label
PC13.GPIO_Label=TIM1CH1N_PH3N
PC13.Mode=Output Compare1 CH1 CH1N
PC13.Signal=TIM1_CH1N
PF0-OSC_IN.GPIOParameters=GPIO_Label
PF0-OSC_IN.GPIO_Label=HSE_IN
PF0-OSC_IN.Mode=HSE-External-Oscillator
PF0-OSC_IN.Signal=RCC_OSC_IN
PF1-OSC_OUT.GPIOParameters=GPIO_Label
PF1-OSC_OUT.GPIO_Label=HSE_OUT
PF1-OSC_OUT.Mode=HSE-External-Oscillator
PF1-OSC_OUT.Signal=RCC_OSC_OUT
RCC.HSE_VALUE=8000000
RCC.SYSCLKFreq_VALUE=16000000
board=custom

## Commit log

2026-02-03 Additionnal documentation
2026-02-03 Kicad Update
2026-02-03 GitIgnore udate
2026-02-05 New docs
2026-02-08 Update on doc and kicad
2026-02-08 Update gate driver
2026-02-10 Update doc and kicad
2026-02-11 Update kicad and docs
2026-02-12 Update kicad and doc
2026-02-15 Kicad and esc choice review
2026-02-15 Excel review
2026-02-19 Excel calculus update
2026-02-21 Final excel version
2026-02-21 Update kicad
2026-02-25 Kicad
2026-03-01 V1 schematic
2026-03-01 First PCB
2026-03-25 Major board update
2026-03-28 Major Kicad Update
2026-03-29 Fix kicad
2026-03-30 Update documentation
2026-03-30 Documentation review
2026-03-30 Apply .gitignore
2026-03-31 Doc Update + Added CubeIDE
2026-03-31 Kicad minor corrections
2026-03-31 G484 -> G474
2026-03-31 Remove kinotes
2026-04-01 Path change for KiCad project
2026-04-01 Licensing on hardware
2026-04-01 Remove old component library
2026-04-01 Clean tracked files now in gitignore
2026-04-01 README update
2026-04-01 Name and README update
2026-04-01 PCB view improvments
2026-04-01 PCB Improvments
2026-04-08 Excel corrections & AN5397 & imgs
2026-04-08 Add img & engineering note
2026-04-08 Add ESC logic draft doc
2026-04-14 Add Cboot Sizing image
